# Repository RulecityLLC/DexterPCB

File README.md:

# DexterPCB
Contains all files needed to create/modify the Dexter custom PCB.

Dexter is a hardware replacement for laserdisc players used in arcade games such as Dragon's Lair.

Dexter is a two board solution: a larger custom PCB that sits on the bottom and a smaller Raspberry Pi v2 the sits on the top.  This repo contains the Eagle files and Bill of Materials spreadsheet to create/modify the custom PCB that sits on the bottom.

The Dexter custom PCB contains two microcontrollers.  The source code for these microcontroller is at https://github.com/RulecityLLC/DexterFirmware .

# PCB
I created this PCB with Eagle v6.  It should work with KiCad's EAGLE importer though I have not tested it.

# Bill of Materials
I included the actual spreadsheet I use when ordering parts for this PCB and assembling this PCB.

# Support
If you need help having PCBs made from the source files or with any other aspect of this repository, I offer commercial support: https://www.daphne-emu.com:9443/mediawiki/index.php/CommercialSupport

--Matt Ownby

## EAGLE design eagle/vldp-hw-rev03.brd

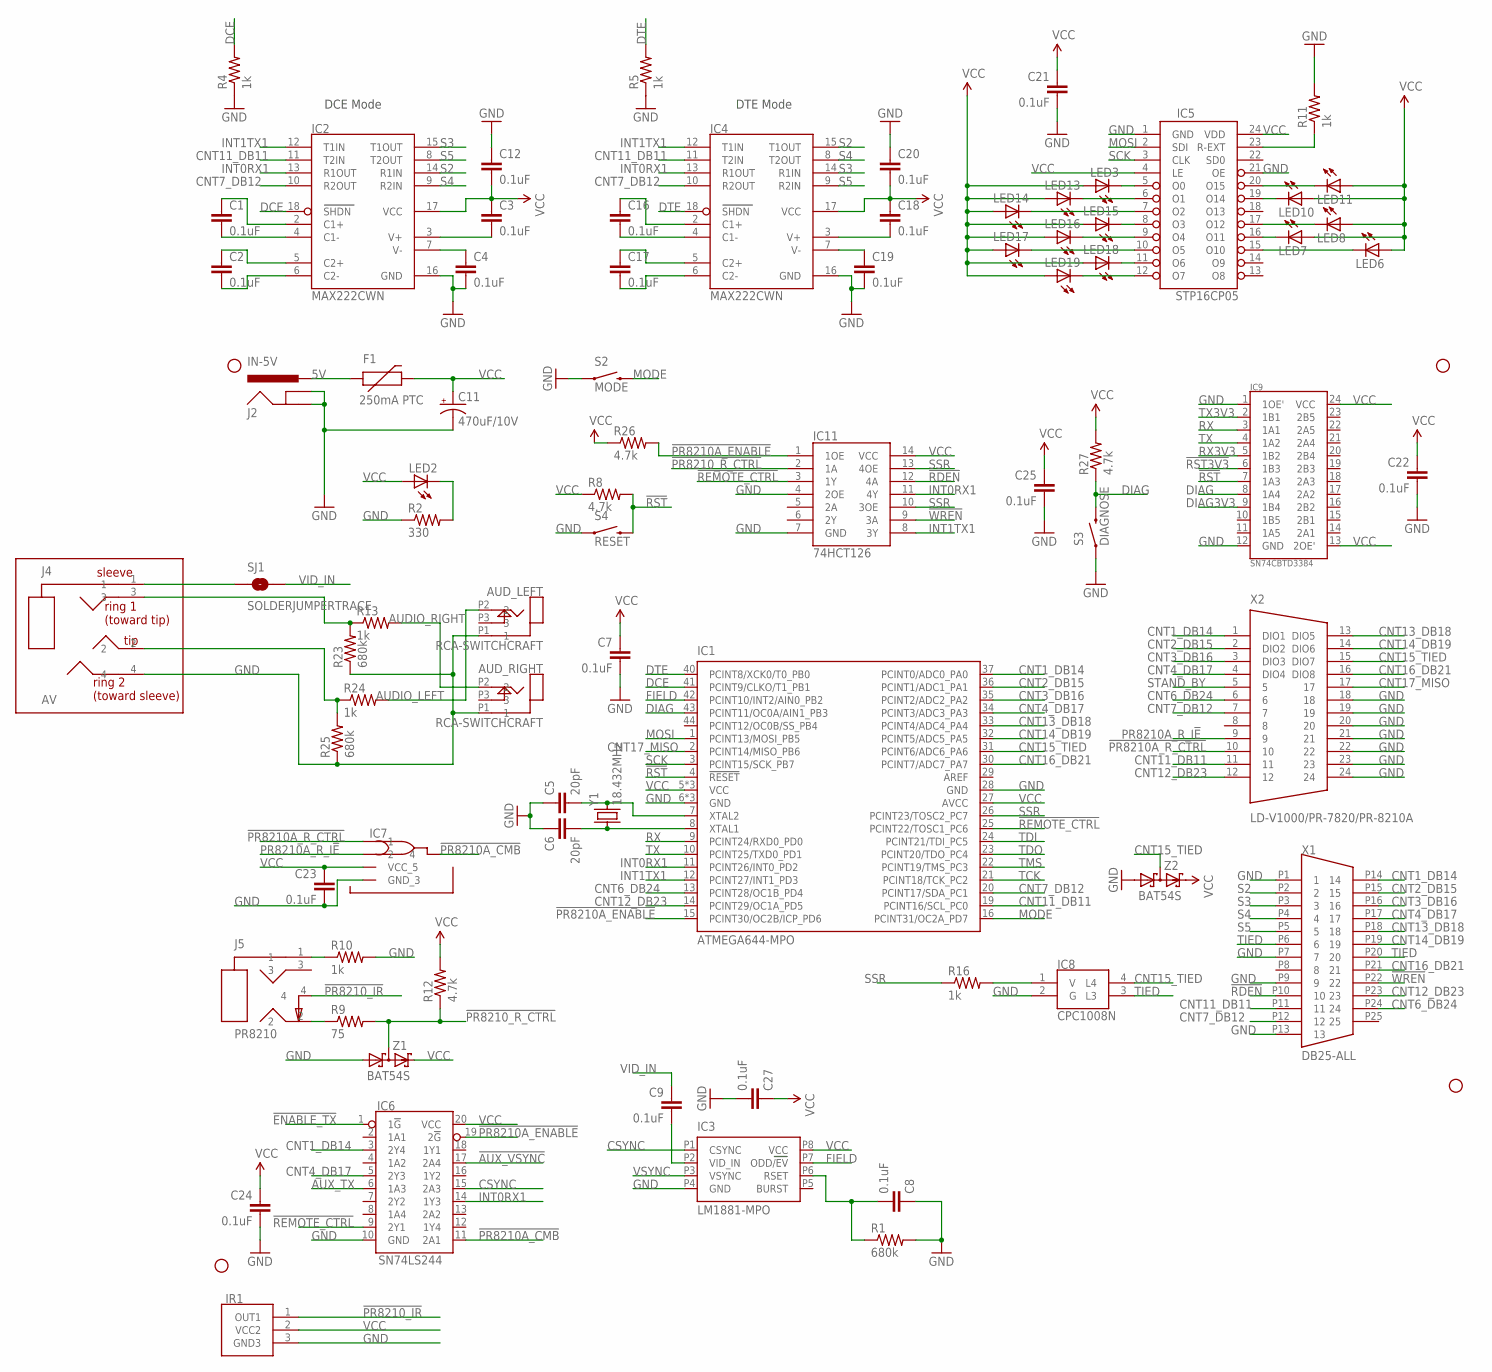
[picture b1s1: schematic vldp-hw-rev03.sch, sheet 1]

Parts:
AUD_LEFT: RCA-SWITCHCRAFT; RCA-SWITCHCRAFT-4X
AUD_RIGHT: RCA-SWITCHCRAFT; RCA-SWITCHCRAFT-4X
C1, C2, C3, C4, C7, C8, C9, C12, C16, C17, C18, C19, C20, C21, C22, C23, C24, C25, C27: 0.1uF; 1206
C5, C6: 20pF; 1206
C11: 470uF/10V; CPOL-RADIAL-10UF-25V
F1: 250mA PTC; PTC
IC1: ATMEGA644-MPO; TQFP44
IC2, IC4: MAX222CWN; SO18
IC3: LM1881-MPO; LM1881M
IC5: STP16CP05; TSSOP24
IC6: SN74LS244; TSSOP20-MPO
IC7: PR8210A_RMT; TSSOP5
IC8: CPC1008N
IC9: SN74CBTD3384; TSSOP24
IC11: 74HCT126; TSSOP14-MPO
IR1: TSOP2438; VISHAY
J2: IN-5V; POWER_JACK_PTH
J4: AV; 3.5MM-SJ-43514
J5: PR8210; 3.5MM-SJ1-3554NG
JP1, JP2, JP3, JP4: STAND-OFF
LED2, LED3, LED6, LED7, LED8, LED10, LED11, LED13, LED14, LED15, LED16, LED17, LED18, LED19: LED1206; LED-1206
R1, R23, R25: 680k; 1206
R2: 330; 1206
R4, R5, R10, R11, R13, R16, R24: 1k; 1206
R8, R12, R26, R27: 4.7k; 1206
R9: 75; 1206
S2: MODE; TACTILE-PTH
S3: DIAGNOSE; TACTILE-PTH
S4: RESET; TACTILE-PTH
SJ1: SOLDERJUMPERTRACE; SJ_2S-TRACE
X1: DB25-ALL; A32077-ND
X2: LD-V1000/PR-7820/PR-8210A; 112-YYY-213R001
Y1: 18.432MHz; CRYSTAL-CSM-3X
Z1, Z2: BAT54S; SOT23

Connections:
5V: F1.P$1 (1), J2.PWR; also elsewhere on the board
!AUX_VSYNC: IC6.17 (2A4); also elsewhere on the board
!ENABLE_TX: IC6.1 (1!G); also elsewhere on the board
!PR8210A_CMB: IC6.11 (2A1), IC7.P$4 (4)
!PR8210A_ENABLE: IC1.15 (PCINT30/OC2B/ICP_PD6), IC6.19 (2!G), IC11.1 (1OE), R26.2
!PR8210A_R_CTRL: IC7.P$1 (1), X2.10
!PR8210_IR: IR1.1 (OUT1), J5.4
!PR8210_R_CTRL: IC11.2 (1A), R9.2, R12.1, Z1.3 (C1A2)
!RDEN: IC11.12 (4A), X1.P10 (10)
!REMOTE_CTRL: IC1.25 (PCINT22/TOSC1_PC6), IC6.9 (2Y1), IC11.3 (1Y)
!RST: IC1.4 (!RESET), IC9.7 (1A3), R8.2, S4.3 (2); also elsewhere on the board
!RST3V3: IC9.6 (1B3); also elsewhere on the board
!WREN: IC11.9 (3A), X1.P22 (22)
AUDIO_LEFT: AUD_LEFT.P2 (2), R24.2; also elsewhere on the board
AUDIO_RIGHT: AUD_RIGHT.P2 (2), R13.2; also elsewhere on the board
AUX_TX: IC6.6 (1A3); also elsewhere on the board
CNT1_DB14: IC1.37 (PCINT0/ADC0_PA0), IC6.3 (2Y4), X1.P14 (14), X2.1 (DIO1)
CNT2_DB15: IC1.36 (PCINT1/ADC1_PA1), X1.P15 (15), X2.2 (DIO2)
CNT3_DB16: IC1.35 (PCINT2/ADC2_PA2), X1.P16 (16), X2.3 (DIO3)
CNT4_DB17: IC1.34 (PCINT3/ADC3_PA3), IC6.5 (2Y3), X1.P17 (17), X2.4 (DIO4)
CNT6_DB24: IC1.13 (PCINT28/OC1B_PD4), X1.P24 (24), X2.6; also elsewhere on the board
CNT7_DB12: IC1.20 (PCINT17/SDA_PC1), IC2.10 (R2OUT), IC4.10 (R2OUT), X1.P12 (12), X2.7
CNT11_DB11: IC1.19 (PCINT16/SCL_PC0), IC2.11 (T2IN), IC4.11 (T2IN), X1.P11 (11), X2.11; also elsewhere on the board
CNT12_DB23: IC1.14 (PCINT29/OC1A_PD5), X1.P23 (23), X2.12; also elsewhere on the board
CNT13_DB18: IC1.33 (PCINT4/ADC4_PA4), X1.P18 (18), X2.13 (DIO5)
CNT14_DB19: IC1.32 (PCINT5/ADC5_PA5), X1.P19 (19), X2.14 (DIO6)
CNT15_TIED: IC1.31 (PCINT6/ADC6_PA6), IC8.4 (L4), X2.15 (DIO7), Z2.3 (C1A2)
CNT16_DB21: IC1.30 (PCINT7/ADC7_PA7), X1.P21 (21), X2.16 (DIO8)
CNT17_MISO: IC1.2 (PCINT14/MISO_PB6), X2.17; also elsewhere on the board
CSYNC: IC3.P1 (CSYNC), IC6.15 (2A3); also elsewhere on the board
DCE: IC1.41 (PCINT9/CLKO/T1_PB1), IC2.18 (SHDN), R4.2; also elsewhere on the board
DIAG: IC1.43 (PCINT11/OC0A/AIN1_PB3), IC9.8 (1A4), R27.1, S3.3 (2); also elsewhere on the board
DIAG3V3: IC9.9 (1B4); also elsewhere on the board
DTE: IC1.40 (PCINT8/XCK0/T0_PB0), IC4.18 (SHDN), R5.2; also elsewhere on the board
FIELD: IC1.42 (PCINT10/INT2/AIN0_PB2), IC3.P7 (ODD/EV); also elsewhere on the board
GND: AUD_LEFT.P1 (1), AUD_RIGHT.P1 (1), C4.2, C5.1, C6.1, C7.2, C8.1, C11.2 (-), C12.1, C19.2, C20.1, C21.2, C22.2, C23.2, C24.2, C25.2, C27.2, IC1.6 (GND), IC1.18 (GND), IC1.28 (GND), IC1.39 (GND), IC2.16 (GND), IC3.P4 (GND), IC4.16 (GND), IC5.1 (GND), IC5.21 (OE), IC6.10 (GND), IC7.P$3 (GND_3), IC8.2 (G), IC9.1 (1OE'), IC9.12 (GND), IC11.4 (2OE), IC11.7 (GND), IR1.3 (GND3), J2.GND, J2.GNDBREAK, J4.4, R1.2, R2.1, R4.1, R5.1, R10.2, R11.2, R23.1, R25.1, S2.1, S3.1, S4.1, X1.P1 (1), X1.P7 (7), X1.P9 (9), X1.P13 (13), X2.18, X2.19, X2.20, X2.21, X2.22, X2.23, X2.24, Z1.1 (A1), Z2.1 (A1); also elsewhere on the board
INT0RX1: IC1.11 (PCINT26/INT0_PD2), IC2.13 (R1OUT), IC4.13 (R1OUT), IC6.14 (1Y3), IC11.11 (4Y); also elsewhere on the board
INT1TX1: IC1.12 (PCINT27/INT1_PD3), IC2.12 (T1IN), IC4.12 (T1IN), IC11.8 (3Y); also elsewhere on the board
MODE: IC1.16 (PCINT31/OC2A_PD7), S2.3 (2)
MOSI: IC1.1 (PCINT13/MOSI_PB5), IC5.2 (SDI); also elsewhere on the board
unnamed: C2.1, IC2.5 (C2+)
unnamed: C5.2, IC1.7 (XTAL2), Y1.P$2
unnamed: C6.2, IC1.8 (XTAL1), Y1.P$1
unnamed: C1.2, IC2.4 (C1-)
unnamed: C1.1, IC2.2 (C1+)
unnamed: IC8.1 (V), R16.2
unnamed: C2.2, IC2.6 (C2-)
unnamed: C16.2, IC4.4 (C1-)
unnamed: J5.1, R10.1
unnamed: C8.2, IC3.P6 (RSET), R1.1
unnamed: C9.2, IC3.P2 (VID_IN)
unnamed: LED2.C, R2.2
unnamed: J4.1, SJ1.1
unnamed: J4.2, R24.1, R25.2
unnamed: IC5.5 (O0), LED3.C
unnamed: IC5.6 (O1), LED13.C
unnamed: IC5.7 (O2), LED14.C
unnamed: IC5.8 (O3), LED15.C
unnamed: C16.1, IC4.2 (C1+)
unnamed: C17.1, IC4.5 (C2+)
unnamed: C17.2, IC4.6 (C2-)
unnamed: IC5.9 (O4), LED16.C
unnamed: IC5.10 (O5), LED17.C
unnamed: IC5.11 (O6), LED18.C
unnamed: IC5.12 (O7), LED19.C
unnamed: J4.3, R13.1, R23.2
unnamed: IC5.15 (O10), LED6.C
unnamed: IC5.16 (O11), LED7.C
unnamed: IC5.17 (O12), LED8.C
unnamed: IC5.19 (O14), LED10.C
unnamed: IC5.20 (O15), LED11.C
unnamed: IC5.23 (R-EXT), R11.1
PR8210A_R_I!E: IC7.P$2 (2), X2.9
PR8210_TIP: J5.2, R9.1
RX: IC1.9 (PCINT24/RXD0_PD0), IC9.3 (1A1); also elsewhere on the board
RX3V3: IC9.5 (1B2); also elsewhere on the board
S2: IC2.14 (R1IN), IC4.15 (T1OUT), X1.P2 (2)
S3: IC2.15 (T1OUT), IC4.14 (R1IN), X1.P3 (3)
S4: IC2.9 (R2IN), IC4.8 (T2OUT), X1.P4 (4)
S5: IC2.8 (T2OUT), IC4.9 (R2IN), X1.P5 (5)
SCK: IC1.3 (PCINT15/SCK_PB7), IC5.3 (CLK); also elsewhere on the board
SSR: IC1.26 (PCINT23/TOSC2_PC7), IC11.10 (3OE), IC11.13 (4OE), R16.1; also elsewhere on the board
STAND_BY: X2.5; also elsewhere on the board
TCK: IC1.21 (PCINT18/TCK_PC2); also elsewhere on the board
TDI: IC1.24 (PCINT21/TDI_PC5); also elsewhere on the board
TDO: IC1.23 (PCINT20/TDO_PC4); also elsewhere on the board
TIED: IC8.3 (L3), X1.P6 (6), X1.P20 (20)
TMS: IC1.22 (PCINT19/TMS_PC3); also elsewhere on the board
TX: IC1.10 (PCINT25/TXD0_PD1), IC9.4 (1A2); also elsewhere on the board
TX3V3: IC9.2 (1B1); also elsewhere on the board
V+1: C3.2, IC2.3 (V+)
V+2: C18.2, IC4.3 (V+)
V-1: C4.1, IC2.7 (V-)
V-2: C19.1, IC4.7 (V-)
VCC: C3.1, C7.1, C11.1 (+), C12.2, C18.1, C20.2, C21.1, C22.1, C23.1, C24.1, C25.1, C27.1, F1.P$2 (2), IC1.5 (VCC), IC1.17 (VCC), IC1.27 (AVCC), IC1.38 (VCC), IC2.17 (VCC), IC3.P8 (VCC), IC4.17 (VCC), IC5.4 (LE), IC5.24 (VDD), IC6.20 (VCC), IC7.P$5 (VCC_5), IC9.13 (2OE'), IC9.24 (VCC), IC11.14 (VCC), IR1.2 (VCC2), LED2.A, LED3.A, LED6.A, LED7.A, LED8.A, LED10.A, LED11.A, LED13.A, LED14.A, LED15.A, LED16.A, LED17.A, LED18.A, LED19.A, R8.1, R12.2, R26.1, R27.2, Z1.2 (C2), Z2.2 (C2); also elsewhere on the board
VID_IN: C9.1, SJ1.2; also elsewhere on the board
VSYNC: IC3.P3 (VSYNC); also elsewhere on the board

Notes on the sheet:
DCE Mode
DTE Mode

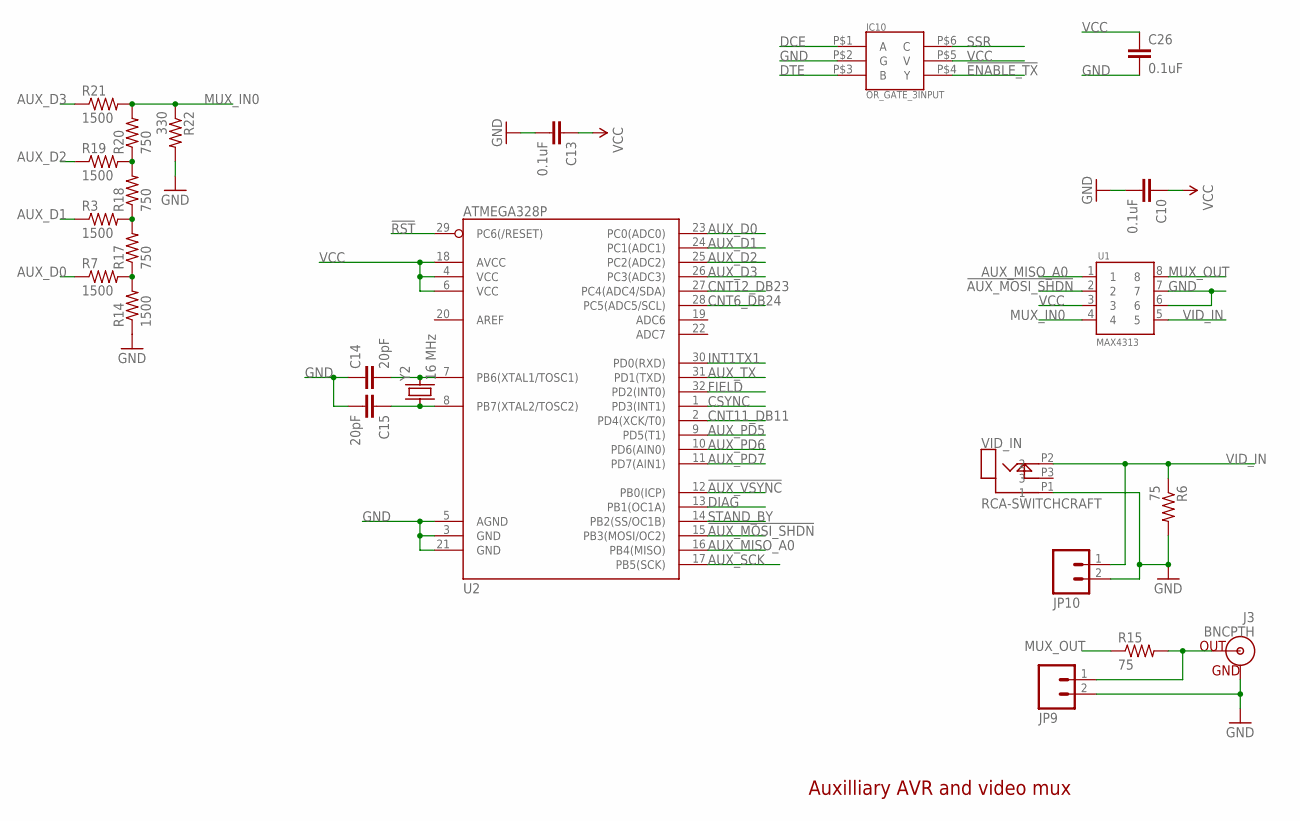
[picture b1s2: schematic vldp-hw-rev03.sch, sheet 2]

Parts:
C10, C13, C26: 0.1uF; 1206
C14, C15: 20pF; 1206
IC10: OR_GATE_3INPUT; TSSOP6-DCK
J3: BNCPTH; BNC
JP9, JP10: M02PTH; 1X02
R3, R7, R14, R19, R21: 1500; 1206
R6, R15: 75; 1206
R17, R18, R20: 750; 1206
R22: 330; 1206
U1: MAX4313; MAXIM-UMAX-LONGPADS
U2: ATMEGA328P; TQFP32-LONGPADS
VID_IN: RCA-SWITCHCRAFT; RCA-SWITCHCRAFT-4X
Y2: 16 MHz; CRYSTAL-CSM-3X

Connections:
!AUX_MOSI_SHDN: U1.2, U2.15 (PB3(MOSI/OC2)); also elsewhere on the board
!AUX_VSYNC: U2.12 (PB0(ICP)); also elsewhere on the board
!ENABLE_TX: IC10.P$4 (Y); also elsewhere on the board
!RST: U2.29 (PC6(/RESET)); also elsewhere on the board
AUX_D0: R7.1, U2.23 (PC0(ADC0))
AUX_D1: R3.1, U2.24 (PC1(ADC1))
AUX_D2: R19.1, U2.25 (PC2(ADC2))
AUX_D3: R21.1, U2.26 (PC3(ADC3))
AUX_MISO_A0: U1.1, U2.16 (PB4(MISO)); also elsewhere on the board
AUX_PD5: U2.9 (PD5(T1)); also elsewhere on the board
AUX_PD6: U2.10 (PD6(AIN0)); also elsewhere on the board
AUX_PD7: U2.11 (PD7(AIN1)); also elsewhere on the board
AUX_SCK: U2.17 (PB5(SCK)); also elsewhere on the board
AUX_TX: U2.31 (PD1(TXD)); also elsewhere on the board
CNT6_DB24: U2.28 (PC5(ADC5/SCL)); also elsewhere on the board
CNT11_DB11: U2.2 (PD4(XCK/T0)); also elsewhere on the board
CNT12_DB23: U2.27 (PC4(ADC4/SDA)); also elsewhere on the board
CSYNC: U2.1 (PD3(INT1)); also elsewhere on the board
DCE: IC10.P$1 (A); also elsewhere on the board
DIAG: U2.13 (PB1(OC1A)); also elsewhere on the board
DTE: IC10.P$3 (B); also elsewhere on the board
FIELD: U2.32 (PD2(INT0)); also elsewhere on the board
GND: C10.2, C13.2, C14.1, C15.2, C26.2, IC10.P$2 (G), J3.GND, JP9.2, JP10.2, R6.2, R14.1, R22.2, U1.6, U1.7, U2.3 (GND), U2.5 (AGND), U2.21 (GND), VID_IN.P1 (1); also elsewhere on the board
INT1TX1: U2.30 (PD0(RXD)); also elsewhere on the board
MUX_IN0: R20.2, R21.2, R22.1, U1.4
MUX_OUT: R15.1, U1.8
unnamed: J3.S (OUT), JP9.1, R15.2
unnamed: R3.2, R17.2, R18.1
unnamed: R7.2, R14.2, R17.1
unnamed: R18.2, R19.2, R20.1
unnamed: C14.2, U2.7 (PB6(XTAL1/TOSC1)), Y2.P$2
unnamed: C15.1, U2.8 (PB7(XTAL2/TOSC2)), Y2.P$1
SSR: IC10.P$6 (C); also elsewhere on the board
STAND_BY: U2.14 (PB2(SS/OC1B)); also elsewhere on the board
VCC: C10.1, C13.1, C26.1, IC10.P$5 (V), U1.3, U2.4 (VCC), U2.6 (VCC), U2.18 (AVCC); also elsewhere on the board
VID_IN: JP10.1, R6.1, U1.5, VID_IN.P2 (2); also elsewhere on the board

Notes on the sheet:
Auxilliary AVR and video mux

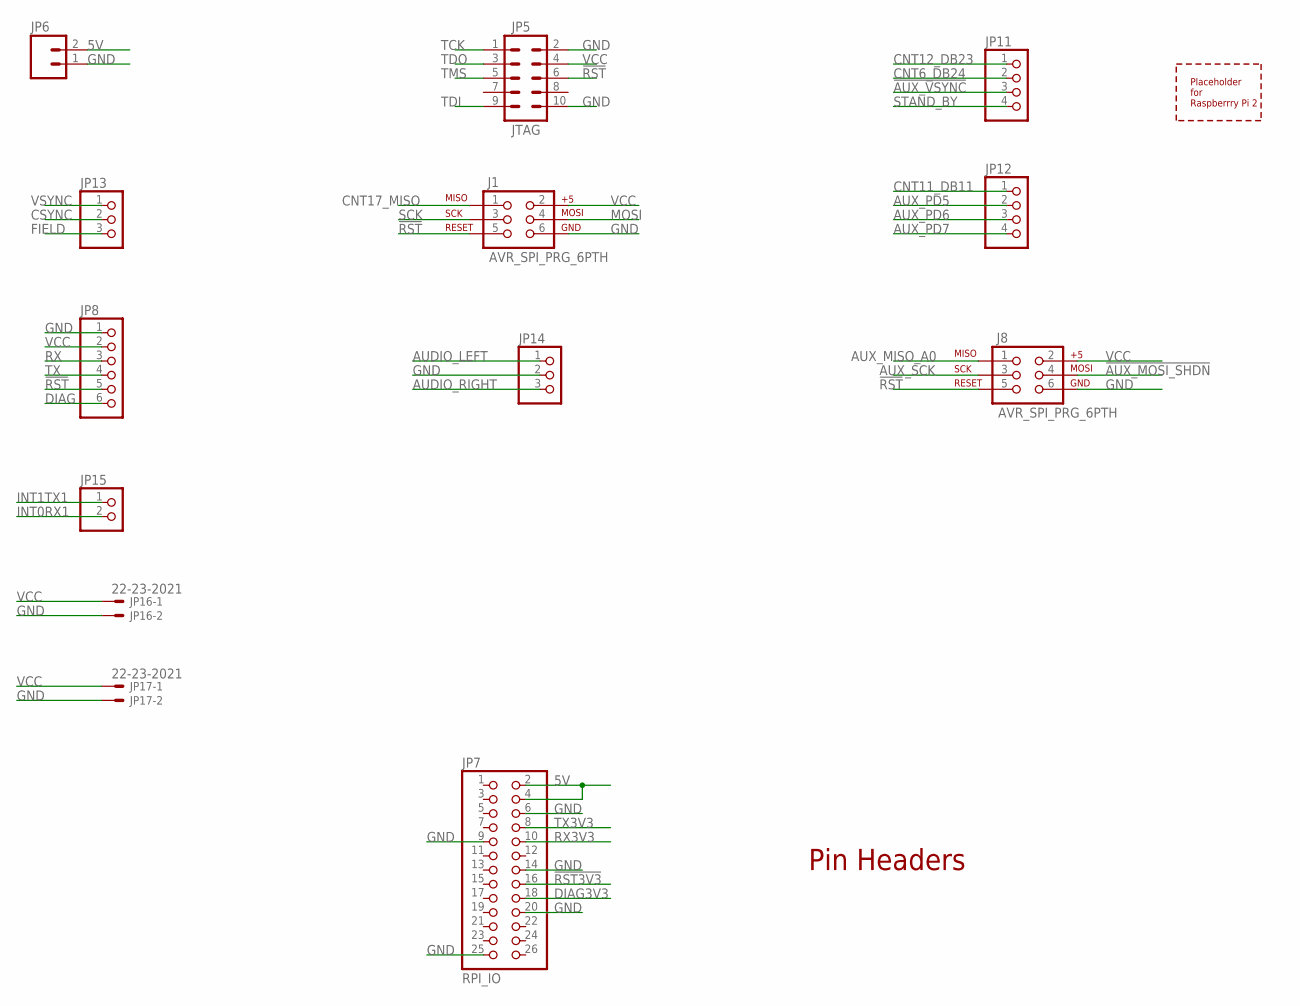
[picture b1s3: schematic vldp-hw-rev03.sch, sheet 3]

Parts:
J1, J8: AVR_SPI_PRG_6PTH; 2X3
JP5: JTAG; AVR_ICSP
JP6: M02PTH; 1X02
JP7: RPI_IO; 2X13
JP8: PINHD-1X6; 1X06
JP11, JP12: PINHD-1X4; 1X04
JP13, JP14: PINHD-1X3; 1X03
JP15: PINHD-1X2; 1X02
JP16, JP17: 22-23-2021
U$1: RASPBERRY_PI2_LAYOUT; RPI2

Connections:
5V: JP6.2, JP7.2, JP7.4; also elsewhere on the board
!AUX_MOSI_SHDN: J8.4; also elsewhere on the board
!AUX_VSYNC: JP11.3; also elsewhere on the board
!RST: J1.5, J8.5, JP5.6, JP8.5; also elsewhere on the board
!RST3V3: JP7.16; also elsewhere on the board
AUDIO_LEFT: JP14.1; also elsewhere on the board
AUDIO_RIGHT: JP14.3; also elsewhere on the board
AUX_MISO_A0: J8.1; also elsewhere on the board
AUX_PD5: JP12.2; also elsewhere on the board
AUX_PD6: JP12.3; also elsewhere on the board
AUX_PD7: JP12.4; also elsewhere on the board
AUX_SCK: J8.3; also elsewhere on the board
CNT6_DB24: JP11.2; also elsewhere on the board
CNT11_DB11: JP12.1; also elsewhere on the board
CNT12_DB23: JP11.1; also elsewhere on the board
CNT17_MISO: J1.1; also elsewhere on the board
CSYNC: JP13.2; also elsewhere on the board
DIAG: JP8.6; also elsewhere on the board
DIAG3V3: JP7.18; also elsewhere on the board
FIELD: JP13.3; also elsewhere on the board
GND: J1.6, J8.6, JP5.2, JP5.10, JP6.1, JP7.6, JP7.9, JP7.14, JP7.20, JP7.25, JP8.1, JP14.2, JP16.2, JP17.2; also elsewhere on the board
INT0RX1: JP15.2; also elsewhere on the board
INT1TX1: JP15.1; also elsewhere on the board
MOSI: J1.4; also elsewhere on the board
RX: JP8.3; also elsewhere on the board
RX3V3: JP7.10; also elsewhere on the board
SCK: J1.3; also elsewhere on the board
STAND_BY: JP11.4; also elsewhere on the board
TCK: JP5.1; also elsewhere on the board
TDI: JP5.9; also elsewhere on the board
TDO: JP5.3; also elsewhere on the board
TMS: JP5.5; also elsewhere on the board
TX: JP8.4; also elsewhere on the board
TX3V3: JP7.8; also elsewhere on the board
VCC: J1.2, J8.2, JP5.4, JP8.2, JP16.1, JP17.1; also elsewhere on the board
VSYNC: JP13.1; also elsewhere on the board

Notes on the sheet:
Pin Headers

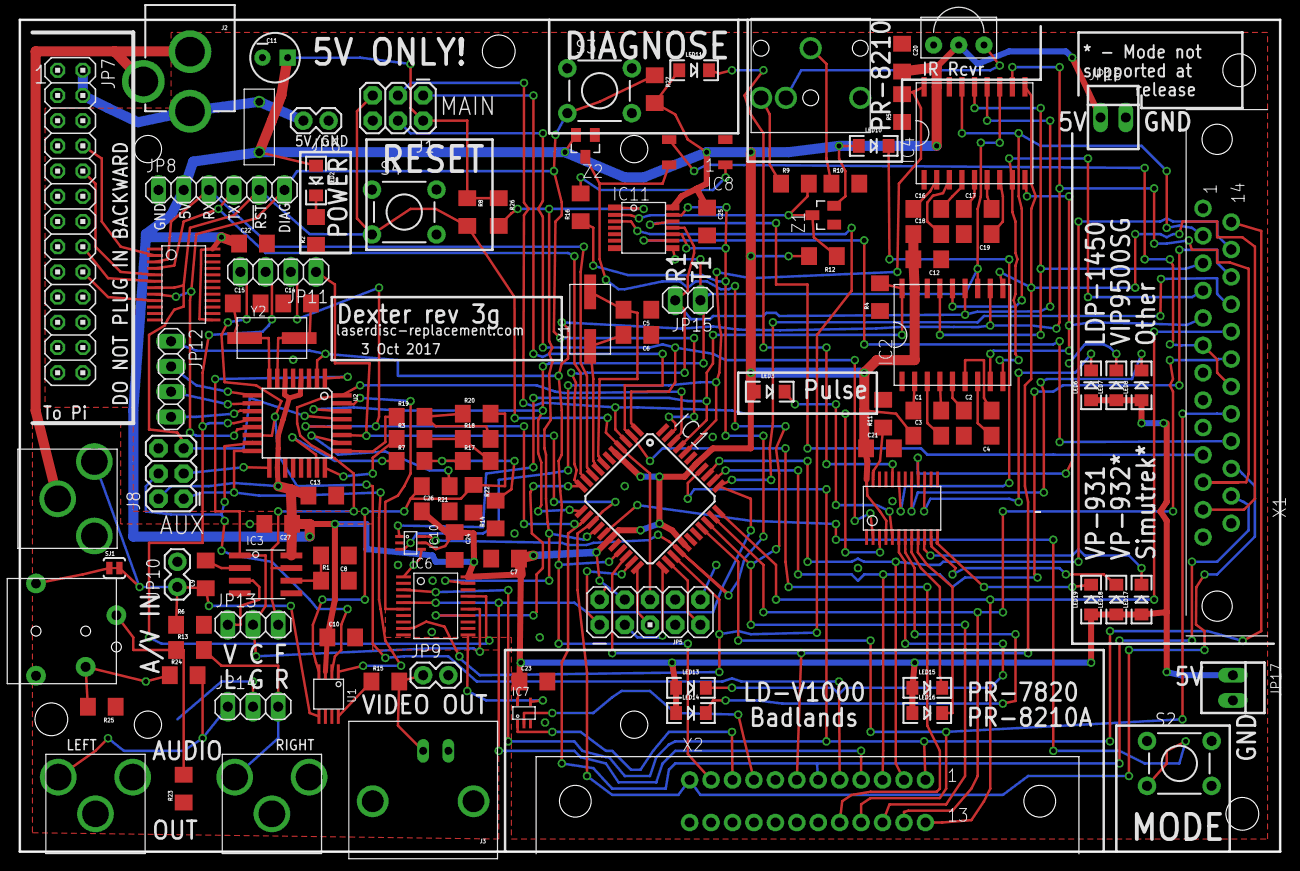
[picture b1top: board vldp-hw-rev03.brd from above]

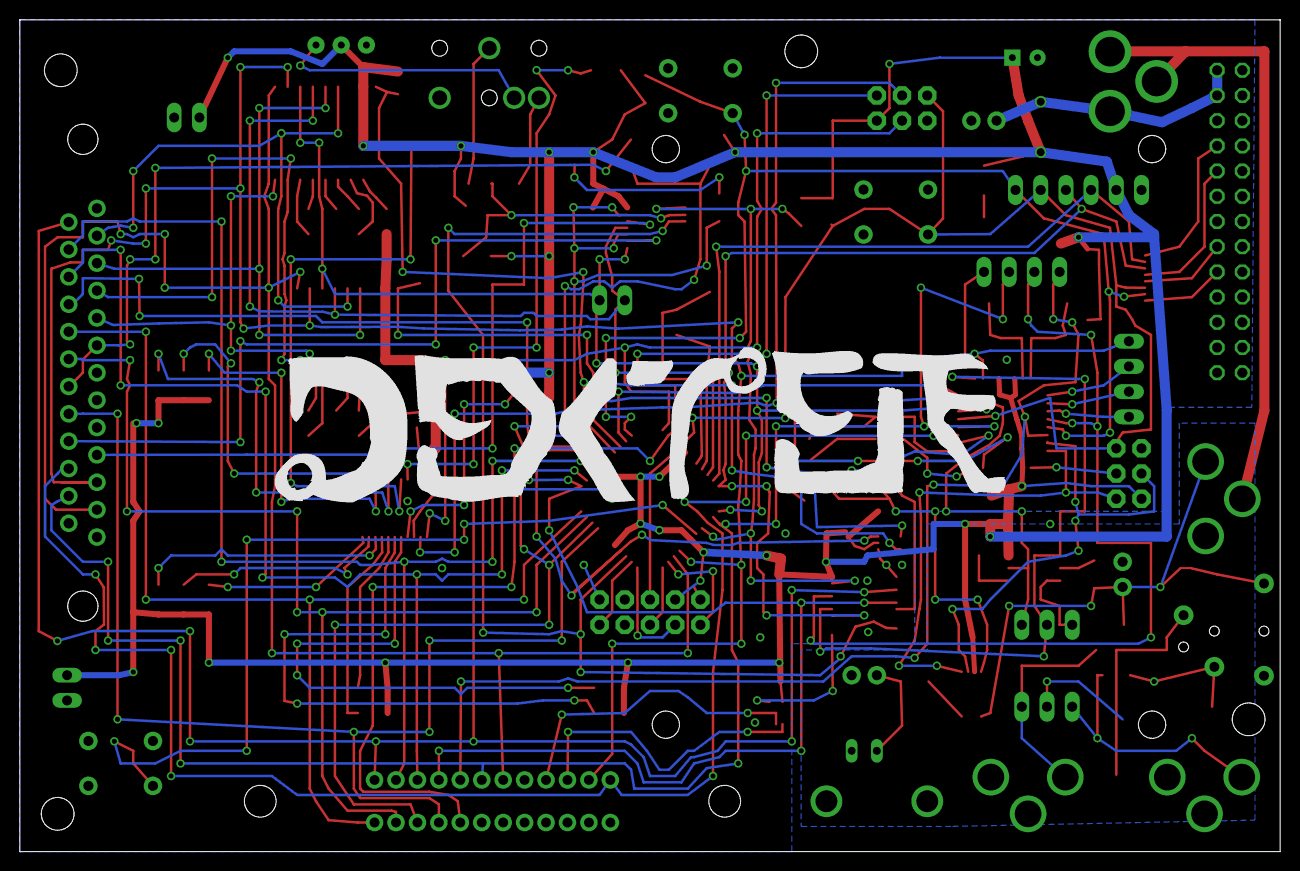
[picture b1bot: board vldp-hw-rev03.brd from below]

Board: 2 copper layers, 127.0 x 83.8 mm, 121 parts (3 on the bottom side), 115 nets.

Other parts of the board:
U$2: DEXTER_LOGO
